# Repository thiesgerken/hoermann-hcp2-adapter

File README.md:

<div align="center">

# Hörmann HCP2 Adapter

**An open carrier PCB and 3D-printable enclosure for connecting an ESP32-C3 to a Hörmann Series 4 garage door opener.**

</div>

<table>
<tr>
<td width="34%" align="center"><br><strong>65 × 44.5 mm carrier PCB</strong></td>
<td width="33%" align="center"><br><strong>Ventilated lid</strong></td>
<td width="33%" align="center"><br><strong>Fitted electronics tray</strong></td>
</tr>
</table>

> [!CAUTION]
> Verify the pinout of your own opener and every conductor of your cable before connecting anything. See [Variants](#variants).
>
> Use this project entirely at your own risk. I am not responsible for any damage, injury, loss, or other consequence resulting from its use in any way. This independent project is not affiliated with, endorsed by, or sponsored by Hörmann.

This is the documentation repository for how I built my adapter around the [ESPHome Hörmann HCP component](https://esphome.io/components/cover/hoermann_hcp/). It may be useful for other people building one as well.

It includes:

- 🧩 a fully routed two-layer KiCad carrier PCB with project-specific footprints
- ⚙️ reproducible Python generators for the schematic, PCB, manufacturing outputs, and renders
- 📦 a compact, parametric build123d enclosure matched directly to the PCB geometry
- 🔌 a ready-to-flash ESPHome configuration with Wi-Fi provisioning
- 🖨️ printable STL files and 3MF assembly previews
- 📚 documented mechanical, electrical, and sourcing decisions

## BOM

### Electronics

| Qty. | Ref. | Component | Notes |
|---:|---|---|---|
| 1 | PCB | Carrier PCB | Two-layer, 65 × 44.5 mm; fabrication files are in [`pcb/`](pcb/) |
| 1 | U1 | [ESP32-C3 Super Mini](reference/docs/purchased-modules.md#esp32-c3-super-mini) | Socketed; runs ESPHome |
| 1 | PS1 | [LM2596 HW-411 buck converter](reference/docs/purchased-modules.md#lm2596-buck-converter-module) | Adjustable; set and verify 5.0 V before connecting U1 |
| 1 | U2 | [Isolated TTL-to-RS485 module](reference/docs/purchased-modules.md#isolated-ttl-to-rs485-module) | 3.3 V/5 V, automatic direction control, integrated 120 Ω termination |
| 1 | J1 | [Unshielded right-angle 6P6C jack](reference/docs/connector-rj12.md) | AliExpress item `1005003078110991`, option `6P6C` |
| 1 | JP1 | 1×2, 2.54 mm pin header and jumper shunt | Disconnects `BUS_PWR` before USB is connected |
| 2 | U1 sockets | 1×8, 2.54 mm socket headers | Keep U1 removable and provide clearance above H4 |
| 1 | W1 | [6P6C cable](reference/docs/purchased-modules.md#6p6c-cable) | Reversed for the `cross` board, straight-through for `straight`. See [Variants](#variants). Verify all six conductors before use |

### Enclosure

| Qty. | Component | Notes |
|---:|---|---|
| 1 | Printed `bottom.stl` | Tray with PCB supports and 6P6C opening |
| 1 | Printed `top.stl` | Ventilated lid |
| 7 | Ruthex M3 heat-set inserts, 5.7 mm long, Ø4.0 mm hole | Four for the lid columns and three for the PCB bosses |
| 4 | M3 × 6 socket cap screws | Lid. Anything longer than 7.5 mm bottoms out in the blind hole |
| 3 | M3 × 6 socket cap screws | PCB. Full thread engagement would need 7.3 mm, and 4.4 mm is ample for M3 |

The LM2596 is not galvanically isolated. The complete adapter therefore shares the HCP supply ground even though the RS485 signal path is isolated. Full galvanic isolation would require an isolated DC/DC converter.

## 🧩 PCB

The [`pcb/`](pcb/) directory is the electrical source of truth. It contains the shared net model, schematic and layout generators, custom footprints, generated KiCad projects, renders, ERC and DRC reports, and fabrication files.

| Property | Value |
|---|---|
| Board | 2 layers, 65 × 44.5 mm |
| Routing | 0.5 mm signals, 0.8 mm power, two vias, three on the straight variant |
| Input | Hörmann HCP2 through a 6P6C jack |
| Controller | Socketed ESP32-C3 Super Mini |
| Power | LM2596 module, approximately 25 V to 5 V |
| Bus interface | Isolated automatic-direction TTL-to-RS485 module |
| Mounting | Three M3 board holes plus one supported corner |

### Variants

Two boards are generated from the same sources. They are identical except for how the six
contacts of J1 map onto the nets, and each one says on its silkscreen which cable it wants.

| Variant | Silkscreen | Cable | J1 contacts |
|---|---|---|---|
| `cross` | `CABLE: X` | Reversed (rollover) | 1, 2 GND · 3 B- · 4 A+ · 5, 6 +25 V |
| `straight` | `CABLE: II` | Straight-through 1:1 | 1, 2 +25 V · 3 A+ · 4 B- · 5, 6 GND |

`cross` follows the pinout in the ESPHome documentation and is the board built and tested
here. The openers measured for this project are mirrored against that pinout, which is why
it needs a reversed cable. `straight` exists for anyone who would rather buy an ordinary
1:1 cable, and for openers that turn out to match it directly.

Measure your own opener before ordering either board. Getting this wrong puts +25 V on the
adapter's ground.

### Layout

| Reference | Part and placement |
|---|---|
| J1 | Amphenol 54601-compatible right-angle 6P6C jack, flush with the top board edge |
| PS1 | 43.4 × 21.2 mm LM2596 HW-411 module, input side toward J1 |
| U2 | 34 × 18 mm isolated RS485 module on castellated pads |
| U1 | ESP32-C3 Super Mini, USB-C flush with the right edge and antenna facing U2 |
| JP1 | `BUS_PWR` disconnect jumper for safe USB use |
| H1, H3, H4 | 3.2 mm M3 mounting holes aligned with the enclosure bosses |

### Generate the design

KiCad must be installed and `kicad-cli` must be available.

```sh
for variant in cross straight; do
  uv run python pcb/schematic.py $variant
  uv run python pcb/pcb.py $variant
done
```

The generators write editable KiCad files directly to [`pcb/`](pcb/), run ERC and DRC, render the schematic and both board sides, and package Gerber and Excellon data. Omitting the argument builds `cross`.

Useful outputs, per variant:

| | Reversed cable | Straight cable |
|---|---|---|
| Editable schematic | [`hcp-cross.kicad_sch`](pcb/hcp-cross.kicad_sch) | [`hcp-straight.kicad_sch`](pcb/hcp-straight.kicad_sch) |
| Schematic PDF | [`hcp-cross-schematic.pdf`](pcb/hcp-cross-schematic.pdf) | [`hcp-straight-schematic.pdf`](pcb/hcp-straight-schematic.pdf) |
| Editable PCB | [`hcp-cross.kicad_pcb`](pcb/hcp-cross.kicad_pcb) | [`hcp-straight.kicad_pcb`](pcb/hcp-straight.kicad_pcb) |
| Layer PDF | [`hcp-cross-pcb.pdf`](pcb/hcp-cross-pcb.pdf) | [`hcp-straight-pcb.pdf`](pcb/hcp-straight-pcb.pdf) |
| Gerber and drill archive | [`hcp-cross-gerbers.zip`](pcb/hcp-cross-gerbers.zip) | [`hcp-straight-gerbers.zip`](pcb/hcp-straight-gerbers.zip) |

The title blocks include the short Git hash of `HEAD`. For release artifacts, commit the sources first, regenerate all four designs, then commit the generated outputs.

## 📦 Enclosure

The [`enclosure/`](enclosure/) directory contains a two-part indoor enclosure generated with [build123d](https://build123d.readthedocs.io/):

- `bottom.stl`: tray with three PCB bosses, a support rail, corner columns, and the 6P6C opening
- `top.stl`: screw-fastened lid with a hexagonal ventilation pattern
- `preview.stl`: open assembly for any STL viewer
- `preview.3mf`: colored assembly with lid and internal hardware

The outer size is **87.8 × 54.3 × 34.0 mm**. Four M3 screws secure the lid into Ruthex threaded inserts. The enclosure is intended for an indoor garage wall and is not waterproof.

PCB dimensions, hole positions, and module placement are imported from [`pcb/pcb.py`](pcb/pcb.py) and the KiCad footprints. Only vertical dimensions and simplified component bodies are maintained separately.

```sh
uv sync
uv run python enclosure/case.py
uv run python enclosure/case.py --show
uv run python enclosure/case.py --png
uv run python enclosure/test_case.py
```

See the [enclosure documentation](enclosure/README.md) for print orientation, clearances, viewer setup, and the mechanical decisions behind the model.

## Assembly notes

Before soldering PS1 onto the carrier board:

1. Power the loose LM2596 module from approximately 25 V with no ESP32 connected.
2. Adjust its output to 5.0 V using the `103` trimmer.
3. Check startup and shutdown behavior under load. The output must not overshoot beyond 5.5 V.
4. Solder PS1 only after those checks pass. Keep `BUS_PWR` open until the remaining board is assembled.

U1 plugs into two 1×8 socket headers. Install the headers, fasten the PCB inside the enclosure, then insert the ESP32. Never connect USB while `BUS_PWR` links the externally supplied 5 V rail.

## HCP2 interface

The ESPHome documentation specifies this pinout for supported Hörmann Series 4 openers:

| Pin | Signal |
|---:|---|
| 1 | GND |
| 2 | GND |
| 3 | B- |
| 4 | A+ |
| 5 | +25 V |
| 6 | +25 V |

The opener's own jack is mirrored against that table: on the ProMatic 4 measured here,
+25 V sits on contacts 1 and 2. The `cross` board follows the table and therefore needs a
**reversed (rollover) cable**, the kind whose two plugs show opposite conductor order when
held identically. The `straight` board mirrors J1 instead and takes a plain 1:1 cable. See
[Variants](#variants).

Measure your opener and every conductor of your cable before the first connection. Pairing
the wrong cable with either board feeds +25 V into the adapter's ground. Doing that here
survived only because the opener limits accessory current to 350 mA.

UART settings: **57600 baud, 8 data bits, even parity, 1 stop bit**. ESPHome participates as a Modbus server. The configuration is in [`esphome/`](esphome/README.md) and uses `GPIO20` for TX and `GPIO21` for RX. That looks reversed next to the net
names on the board, and it is not: U2's TTL pads carry the module's own pin names, so
its `TX` pad drives the ESP32 rather than being driven by it.

## Troubleshooting

The bus offers a hostile debugging environment: it carries power only during a bus scan,
and the opener cuts it again within seconds when the adapter fails to register. That is
too short to read a log. These checks all work on the bench instead, with the board on a
25 V supply and the bus disconnected.

**Does the transmitter work?** Send continuously and measure the DC average, which a plain
multimeter resolves. A temporary `interval` writing 128 zero bytes every 30 ms keeps the
line low about 80 % of the time. Measure between U2's A and B pads:

| A against B | Meaning |
|---|---|
| about 185 mV, unchanged while sending | The driver never switches on. Check the pin roles first |
| moves to roughly 1.6 V while sending | Transmit path is good |
| exactly 0.000 V | The isolated side is not running. The module is dead or unpowered |

The 185 mV is the module's fail-safe bias, so seeing it at all proves the isolated side
has power.

**Does the receiver work?** With the bus disconnected, GPIO21 must sit at a steady 3.3 V.
That is U2's receiver output holding the UART idle level. A wandering level below 0.5 V
means the receiver output is not driving, or the castellated joint is cold.

**Is anything arriving from the bus?** Count bytes instead of logging them. A `uart:`
`debug:` block with a custom `sequence` replaces the default hex dump, so it costs no log
traffic, and a global written to flash with `global_preferences->sync()` survives the
supply being cut. Drive the onboard LED from it and the answer is readable in the garage
without a host attached. Set `dummy_receiver: true` while measuring so the counter does
not depend on Modbus draining the UART, and back to `false` for normal operation.

**Verify the counter before trusting it.** Point the UART at two free neighbouring pins,
GPIO4 and GPIO3, and bridge them. Crosstalk from the transmitting pin is enough to make
the counter run even without the bridge.

## ⚠️ Safety and operating constraints

- Scope is limited to supported Hörmann Series 4 HCP2 devices.
- Disconnect mains power and any emergency battery before installation.
- HCP2 accessories must not be connected or removed while powered.
- Interrupted communication or an ESPHome restart can temporarily block the opener. Power-cycling the opener clears this condition.
- The bus provides approximately 25 V only during a bus scan. The adapter must boot and respond in time.
- Verify the actual jack contact order and every conductor of the cable before first connection, and check that the cable matches the variant printed on the board.
- The selected RS485 module reportedly includes 120 Ω termination. Measure A-to-B resistance with power removed before use. Do not fit a second termination.
- Hörmann specifies a combined 350 mA accessory limit. Measure adapter startup and operating current.

## Repository map

```text
assembled.jpg        Photo of the assembled adapter
LICENSE              MIT, except for the archived third-party material
pcb/                 PCB, schematic, footprints, and fabrication outputs
enclosure/           Parametric enclosure source and printable files
esphome/             ESPHome configuration for the ESP32-C3
reference/docs/      Design records, component notes, and source analysis
reference/           Archived vendor pages, manuals, and datasheets
TODO.md              Open checks, currently none
```

Reference material is intentionally separated from the project deliverables. Start with [`pcb/`](pcb/), [`enclosure/`](enclosure/), and [`esphome/`](esphome/); use [`reference/docs/`](reference/docs/) when a design decision or source needs review.

## License

[MIT](LICENSE), covering the PCB, the enclosure, the generators, the ESPHome
configuration, and the documentation.

[`reference/`](reference/README.md) is excluded. It archives manuals, datasheets, and
vendor listings that belong to their respective owners, with the exception of
[`reference/docs/`](reference/docs/), which is mine and follows the license above.

## Documentation

- [Enclosure design](enclosure/README.md)
- [Firmware](esphome/README.md)
- [Open checks](TODO.md)
- [Components and sourcing status](reference/docs/components.md)
- [Purchased modules](reference/docs/purchased-modules.md)
- [Selected 6P6C jack](reference/docs/connector-rj12.md)
- [Hörmann manual analysis](reference/docs/hoermann-manuals.md)
- [Sources and references](reference/docs/references.md)
- [Decision log](reference/docs/decisions.md)
- [Local vendor archive](reference/README.md)

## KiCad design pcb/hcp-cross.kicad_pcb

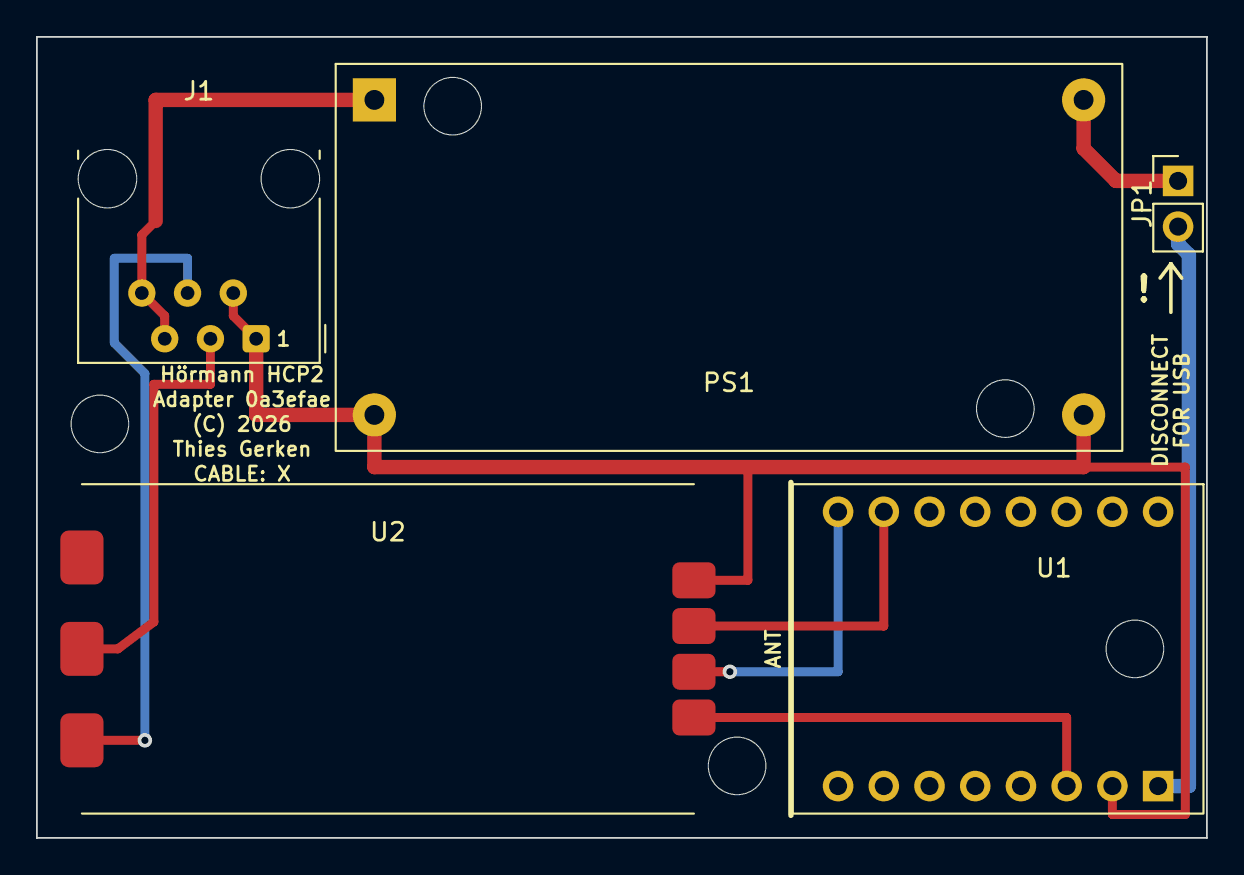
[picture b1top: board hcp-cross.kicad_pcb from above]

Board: 2 copper layers, 65.0 x 44.5 mm, 8 parts (0 on the bottom side), 9 nets.

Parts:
H1, H3, H4: M3; MountingHole_3.2mm_NoCourtyard
J1: HCP2 6P6C; RJ12_Amphenol_54601-x06_Horizontal
JP1: BUS_PWR; PinHeader_1x02_P2.54mm_Vertical
PS1: LM2596 HW-411; LM2596_HW-411
U1: ESP32-C3 Super Mini; ESP32-C3_SuperMini
U2: Isolated RS485; RS485_Isolated_34x18

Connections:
BUCK_5V: JP1.1, PS1.3
ESP_3V3: U1.5, U2.1
ESP_5V: JP1.2, U1.1
HCP_25V: J1.5, J1.6, PS1.1
HCP_A_PLUS: J1.4, U2.5
HCP_B_MINUS: J1.3, U2.6
HCP_GND: J1.1, J1.2, PS1.2, PS1.4, U1.3, U2.4
UART_RX_GPIO21: U1.16, U2.2
UART_TX_GPIO20: U1.14, U2.3

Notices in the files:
pcb/hcp-cross.kicad_pcb:
(C) 2026
